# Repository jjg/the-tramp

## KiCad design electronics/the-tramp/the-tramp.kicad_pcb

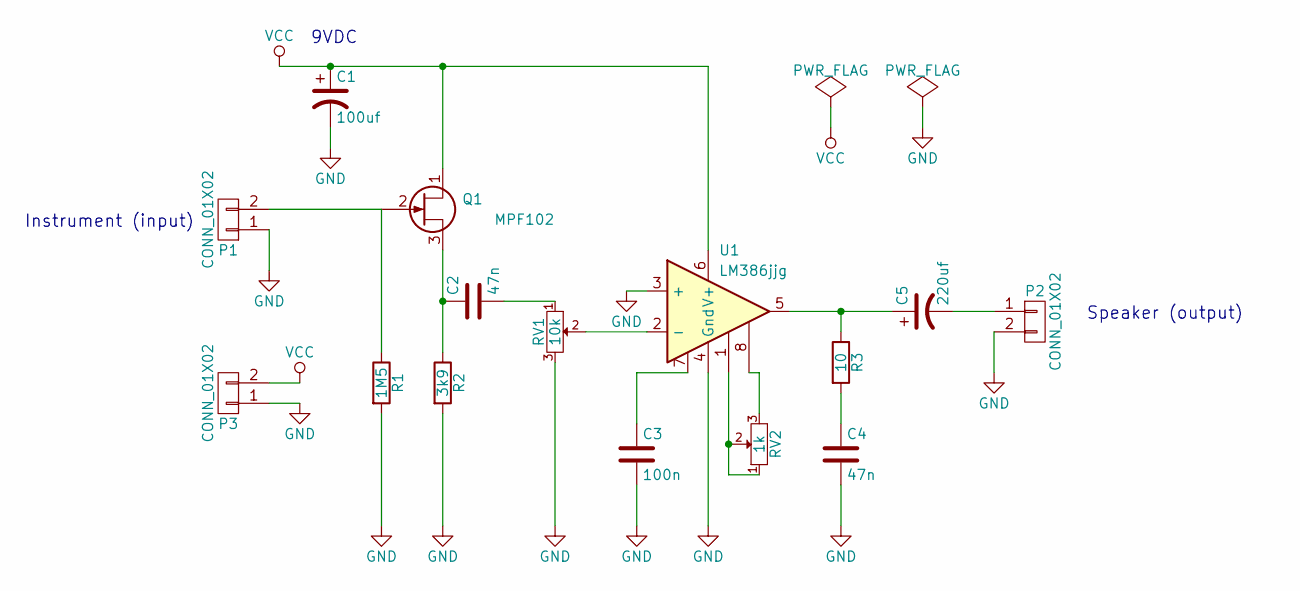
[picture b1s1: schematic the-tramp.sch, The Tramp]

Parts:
C1: 100uf; C_Radial_D8_L11.5_P3.5
C2, C4: 47n; C_Rect_L7.5_W6.5_P5
C3: 100n; C_Rect_L7.5_W6.5_P5
C5: 220uf; C_Radial_D8_L11.5_P3.5
P1, P2, P3: CONN_01X02; Pin_Header_Straight_1x02
Q1: MPF102; TO-92_Inline_Wide
R1: 1M5; R3
R2: 3k9; R3
R3: 10; R3
RV1: 10k; Potentiometer_Alps-RK16-single_largePads
RV2: 1k; Potentiometer_Alps-RK16-single_largePads
U1: LM386jjg; DIP-8_W7.62mm_LongPads

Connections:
GND: C1.2, C3.2, C4.2, P1.1, P2.2, P3.1, R1.2, R2.2, RV1.3, U1.3 (+), U1.4 (Gnd)
unnamed: C2.1, Q1.3 (S), R2.1
unnamed: C2.2, RV1.1
unnamed: C3.1, U1.7
unnamed: C4.1, R3.2
unnamed: C5.1, R3.1, U1.5
unnamed: C5.2, P2.1
unnamed: P1.2, Q1.2 (G), R1.1
unnamed: RV1.2, U1.2 (-)
unnamed: RV2.1, RV2.2, U1.1
unnamed: RV2.3, U1.8
VCC: C1.1, P3.2, Q1.1 (D), U1.6 (V+)

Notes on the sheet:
9VDC
Instrument (input)
Speaker (output)

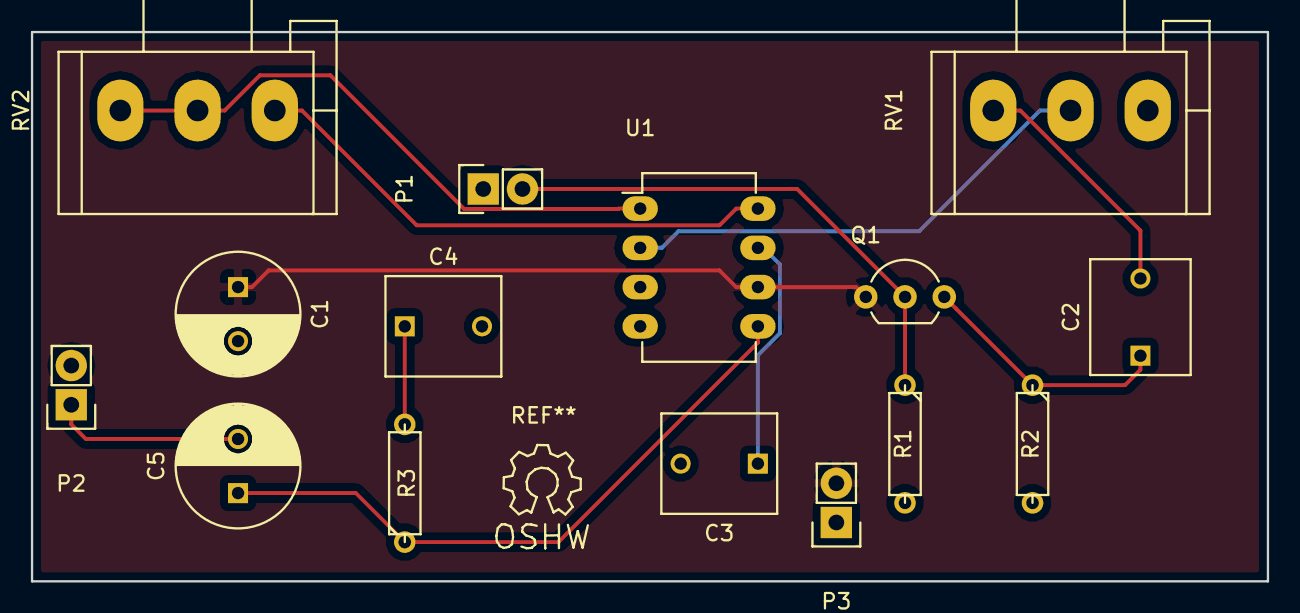
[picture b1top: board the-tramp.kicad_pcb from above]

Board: 2 copper layers, 80.0 x 35.6 mm, 15 parts (0 on the bottom side), 12 nets.

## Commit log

2018-04-20 Add README.md
2018-04-20 Add LICENSE
2018-04-20 Add CHANGELOG
2018-04-20 Initial schematic.
2018-04-20 Made a custom LM386 that includes pin 7.
2018-04-20 First run at laying out the board.
2018-04-20 Added power connector and copper fills.
